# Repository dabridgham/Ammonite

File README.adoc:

= Ammonite

Ammonite is an FPGA development board designed to be useful for
building FPGA-based computers.  It was originally designed to be a
platform for my FPGA PDP-10 but it ought to be useful for just about
anyone who's building their own computer with an FPGA.

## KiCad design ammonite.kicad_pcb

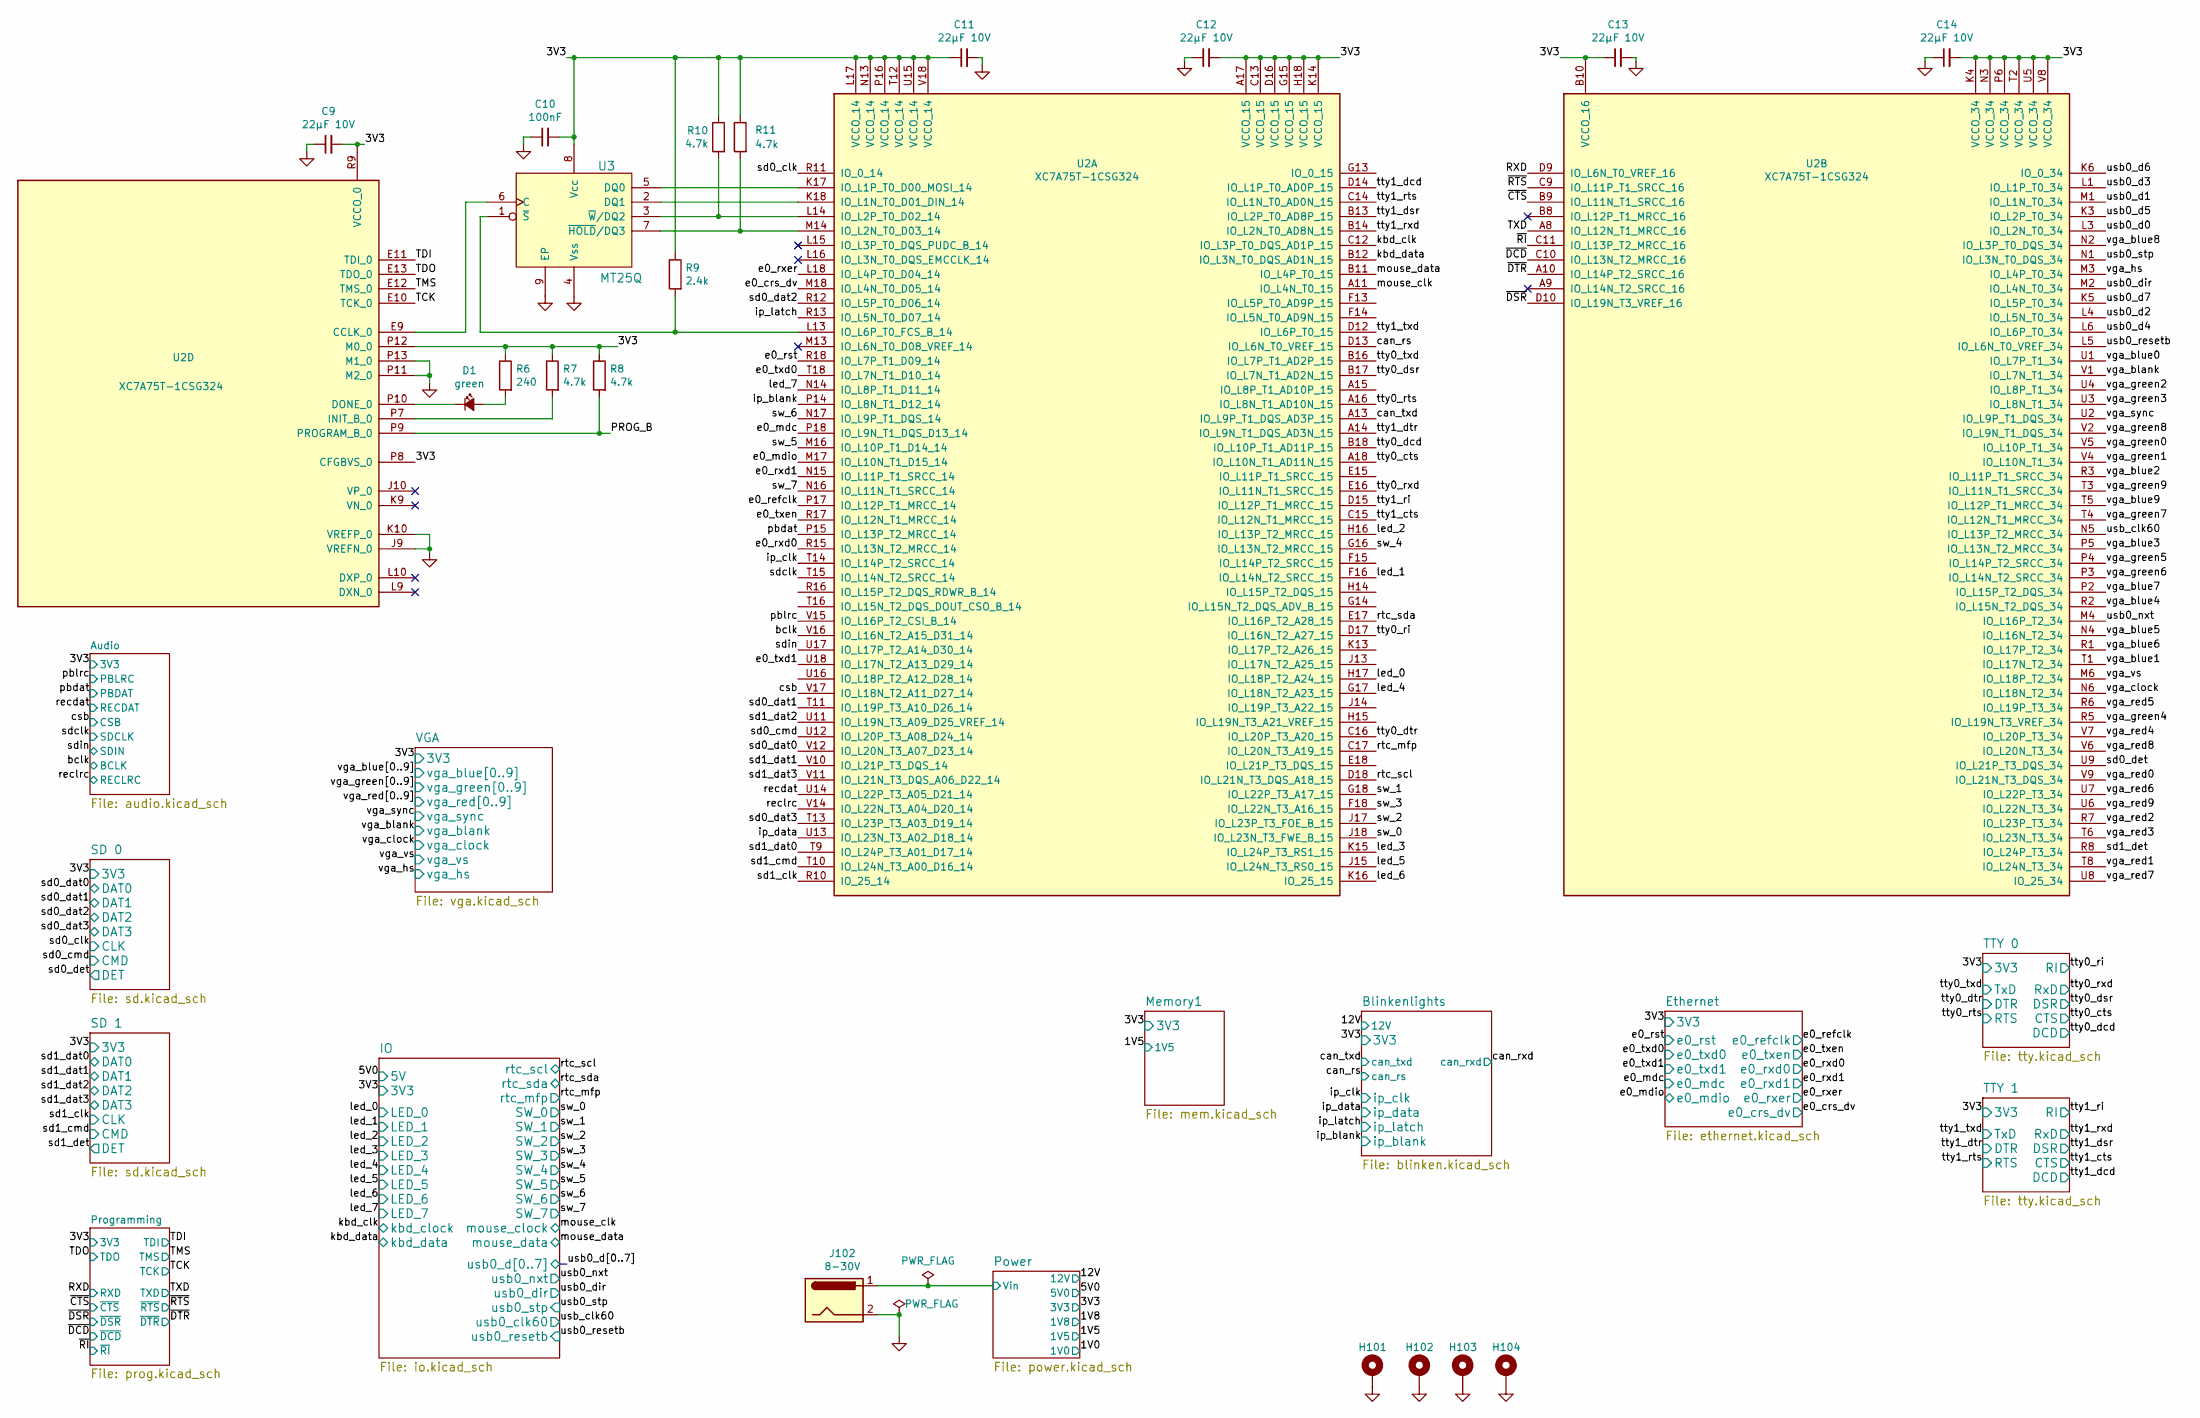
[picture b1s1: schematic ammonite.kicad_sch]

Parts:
C9, C11, C12, C13, C14: 22µF 10V; C_0603_1608Metric
C10: 100nF; C_0603_1608Metric
D1: green; LED_0603_1608Metric
H101, H102, H103, H104: MountingHole_Pad; MountingHole_3.2mm_M3_DIN965_Pad
J102: 8-30V; BarrelJack_CUI_PJ-063AH_Horizontal
R6: 240; R_0603_1608Metric
R7, R8, R10, R11: 4.7k; R_0603_1608Metric
R9: 2.4k; R_0603_1608Metric
U2: XC7A75T-1CSG324; Xilinx_CSG324
U3: MT25Q; DFN-8-1EP_6x5mm_P1.27mm_EP4x4mm

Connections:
/3V3: C9.2, C10.2, C11.1, C12.2, C13.1, C14.2, R6.1, R7.1, R8.1, R9.1, R10.1, R11.1, U2.A17 (VCCO_15), U2.B10 (VCCO_16), U2.C13 (VCCO_15), U2.D16 (VCCO_15), U2.G15 (VCCO_15), U2.H18 (VCCO_15), U2.K4 (VCCO_34), U2.K14 (VCCO_15), U2.L17 (VCCO_14), U2.N3 (VCCO_34), U2.N13 (VCCO_14), U2.P6 (VCCO_34), U2.P8 (CFGBVS_0), U2.P12 (M0_0), U2.P16 (VCCO_14), U2.R9 (VCCO_0), U2.T2 (VCCO_34), U2.T12 (VCCO_14), U2.U5 (VCCO_34), U2.U15 (VCCO_14), U2.V8 (VCCO_34), U2.V18 (VCCO_14), U3.8 (Vcc); also elsewhere on the board
/PROG_B: R8.2, U2.P9 (PROGRAM_B_0)
/Power/Vin: J102.1; also elsewhere on the board
/RXD: U2.D9 (IO_L6N_T0_VREF_16); also elsewhere on the board
/TCK: U2.E10 (TCK_0); also elsewhere on the board
/TDI: U2.E11 (TDI_0); also elsewhere on the board
/TDO: U2.E13 (TDO_0); also elsewhere on the board
/TMS: U2.E12 (TMS_0); also elsewhere on the board
/TXD: U2.A8 (IO_L12N_T1_MRCC_16); also elsewhere on the board
/bclk: U2.V16 (IO_L16N_T2_A15_D31_14); also elsewhere on the board
/can_rs: U2.D13 (IO_L6N_T0_VREF_15); also elsewhere on the board
/can_txd: U2.A13 (IO_L9P_T1_DQS_AD3P_15); also elsewhere on the board
/csb: U2.V17 (IO_L18N_T2_A11_D27_14); also elsewhere on the board
/e0_crs_dv: U2.M18 (IO_L4N_T0_D05_14); also elsewhere on the board
/e0_mdc: U2.P18 (IO_L9N_T1_DQS_D13_14); also elsewhere on the board
/e0_mdio: U2.M17 (IO_L10N_T1_D15_14); also elsewhere on the board
/e0_refclk: U2.P17 (IO_L12P_T1_MRCC_14); also elsewhere on the board
/e0_rst: U2.R18 (IO_L7P_T1_D09_14); also elsewhere on the board
/e0_rxd0: U2.R15 (IO_L13N_T2_MRCC_14); also elsewhere on the board
/e0_rxd1: U2.N15 (IO_L11P_T1_SRCC_14); also elsewhere on the board
/e0_rxer: U2.L18 (IO_L4P_T0_D04_14); also elsewhere on the board
/e0_txd0: U2.T18 (IO_L7N_T1_D10_14); also elsewhere on the board
/e0_txd1: U2.U18 (IO_L17N_T2_A13_D29_14); also elsewhere on the board
/e0_txen: U2.R17 (IO_L12N_T1_MRCC_14); also elsewhere on the board
/ip_blank: U2.P14 (IO_L8N_T1_D12_14); also elsewhere on the board
/ip_clk: U2.T14 (IO_L14P_T2_SRCC_14); also elsewhere on the board
/ip_data: U2.U13 (IO_L23N_T3_A02_D18_14); also elsewhere on the board
/ip_latch: U2.R13 (IO_L5N_T0_D07_14); also elsewhere on the board
/kbd_clk: U2.C12 (IO_L3P_T0_DQS_AD1P_15); also elsewhere on the board
/kbd_data: U2.B12 (IO_L3N_T0_DQS_AD1N_15); also elsewhere on the board
/led_0: U2.H17 (IO_L18P_T2_A24_15); also elsewhere on the board
/led_1: U2.F16 (IO_L14N_T2_SRCC_15); also elsewhere on the board
/led_2: U2.H16 (IO_L13P_T2_MRCC_15); also elsewhere on the board
/led_3: U2.K15 (IO_L24P_T3_RS1_15); also elsewhere on the board
/led_4: U2.G17 (IO_L18N_T2_A23_15); also elsewhere on the board
/led_5: U2.J15 (IO_L24N_T3_RS0_15); also elsewhere on the board
/led_6: U2.K16 (IO_25_15); also elsewhere on the board
/led_7: U2.N14 (IO_L8P_T1_D11_14); also elsewhere on the board
/mouse_clk: U2.A11 (IO_L4N_T0_15); also elsewhere on the board
/mouse_data: U2.B11 (IO_L4P_T0_15); also elsewhere on the board
/pbdat: U2.P15 (IO_L13P_T2_MRCC_14); also elsewhere on the board
/pblrc: U2.V15 (IO_L16P_T2_CSI_B_14); also elsewhere on the board
/recdat: U2.U14 (IO_L22P_T3_A05_D21_14); also elsewhere on the board
/reclrc: U2.V14 (IO_L22N_T3_A04_D20_14); also elsewhere on the board
/rtc_mfp: U2.C17 (IO_L20N_T3_A19_15); also elsewhere on the board
/rtc_scl: U2.D18 (IO_L21N_T3_DQS_A18_15); also elsewhere on the board
/rtc_sda: U2.E17 (IO_L16P_T2_A28_15); also elsewhere on the board
/sd0_clk: U2.R11 (IO_0_14); also elsewhere on the board
/sd0_cmd: U2.U12 (IO_L20P_T3_A08_D24_14); also elsewhere on the board
/sd0_dat0: U2.V12 (IO_L20N_T3_A07_D23_14); also elsewhere on the board
/sd0_dat1: U2.T11 (IO_L19P_T3_A10_D26_14); also elsewhere on the board
/sd0_dat2: U2.R12 (IO_L5P_T0_D06_14); also elsewhere on the board
/sd0_dat3: U2.T13 (IO_L23P_T3_A03_D19_14); also elsewhere on the board
/sd0_det: U2.U9 (IO_L21P_T3_DQS_34); also elsewhere on the board
/sd1_clk: U2.R10 (IO_25_14); also elsewhere on the board
/sd1_cmd: U2.T10 (IO_L24N_T3_A00_D16_14); also elsewhere on the board
/sd1_dat0: U2.T9 (IO_L24P_T3_A01_D17_14); also elsewhere on the board
/sd1_dat1: U2.V10 (IO_L21P_T3_DQS_14); also elsewhere on the board
/sd1_dat2: U2.U11 (IO_L19N_T3_A09_D25_VREF_14); also elsewhere on the board
/sd1_dat3: U2.V11 (IO_L21N_T3_DQS_A06_D22_14); also elsewhere on the board
/sd1_det: U2.R8 (IO_L24P_T3_34); also elsewhere on the board
/sdclk: U2.T15 (IO_L14N_T2_SRCC_14); also elsewhere on the board
/sdin: U2.U17 (IO_L17P_T2_A14_D30_14); also elsewhere on the board
/sw_0: U2.J18 (IO_L23N_T3_FWE_B_15); also elsewhere on the board
/sw_1: U2.G18 (IO_L22P_T3_A17_15); also elsewhere on the board
/sw_2: U2.J17 (IO_L23P_T3_FOE_B_15); also elsewhere on the board
/sw_3: U2.F18 (IO_L22N_T3_A16_15); also elsewhere on the board
/sw_4: U2.G16 (IO_L13N_T2_MRCC_15); also elsewhere on the board
/sw_5: U2.M16 (IO_L10P_T1_D14_14); also elsewhere on the board
/sw_6: U2.N17 (IO_L9P_T1_DQS_14); also elsewhere on the board
/sw_7: U2.N16 (IO_L11N_T1_SRCC_14); also elsewhere on the board
/tty0_cts: U2.A18 (IO_L10N_T1_AD11N_15); also elsewhere on the board
/tty0_dcd: U2.B18 (IO_L10P_T1_AD11P_15); also elsewhere on the board
/tty0_dsr: U2.B17 (IO_L7N_T1_AD2N_15); also elsewhere on the board
/tty0_dtr: U2.C16 (IO_L20P_T3_A20_15); also elsewhere on the board
/tty0_ri: U2.D17 (IO_L16N_T2_A27_15); also elsewhere on the board
/tty0_rts: U2.A16 (IO_L8N_T1_AD10N_15); also elsewhere on the board
/tty0_rxd: U2.E16 (IO_L11N_T1_SRCC_15); also elsewhere on the board
/tty0_txd: U2.B16 (IO_L7P_T1_AD2P_15); also elsewhere on the board
/tty1_cts: U2.C15 (IO_L12N_T1_MRCC_15); also elsewhere on the board
/tty1_dcd: U2.D14 (IO_L1P_T0_AD0P_15); also elsewhere on the board
/tty1_dsr: U2.B13 (IO_L2P_T0_AD8P_15); also elsewhere on the board
/tty1_dtr: U2.A14 (IO_L9N_T1_DQS_AD3N_15); also elsewhere on the board
/tty1_ri: U2.D15 (IO_L12P_T1_MRCC_15); also elsewhere on the board
/tty1_rts: U2.C14 (IO_L1N_T0_AD0N_15); also elsewhere on the board
/tty1_rxd: U2.B14 (IO_L2N_T0_AD8N_15); also elsewhere on the board
/tty1_txd: U2.D12 (IO_L6P_T0_15); also elsewhere on the board
/usb0_d0: U2.L3 (IO_L2N_T0_34); also elsewhere on the board
/usb0_d1: U2.M1 (IO_L1N_T0_34); also elsewhere on the board
/usb0_d2: U2.L4 (IO_L5N_T0_34); also elsewhere on the board
/usb0_d3: U2.L1 (IO_L1P_T0_34); also elsewhere on the board
/usb0_d4: U2.L6 (IO_L6P_T0_34); also elsewhere on the board
/usb0_d5: U2.K3 (IO_L2P_T0_34); also elsewhere on the board
/usb0_d6: U2.K6 (IO_0_34); also elsewhere on the board
/usb0_d7: U2.K5 (IO_L5P_T0_34); also elsewhere on the board
/usb0_dir: U2.M2 (IO_L4N_T0_34); also elsewhere on the board
/usb0_nxt: U2.M4 (IO_L16P_T2_34); also elsewhere on the board
/usb0_resetb: U2.L5 (IO_L6N_T0_VREF_34); also elsewhere on the board
/usb0_stp: U2.N1 (IO_L3N_T0_DQS_34); also elsewhere on the board
/usb_clk60: U2.N5 (IO_L13P_T2_MRCC_34); also elsewhere on the board
/vga_blank: U2.V1 (IO_L7N_T1_34); also elsewhere on the board
/vga_blue0: U2.U1 (IO_L7P_T1_34); also elsewhere on the board
/vga_blue1: U2.T1 (IO_L17N_T2_34); also elsewhere on the board
/vga_blue2: U2.R3 (IO_L11P_T1_SRCC_34); also elsewhere on the board
/vga_blue3: U2.P5 (IO_L13N_T2_MRCC_34); also elsewhere on the board
/vga_blue4: U2.R2 (IO_L15N_T2_DQS_34); also elsewhere on the board
/vga_blue5: U2.N4 (IO_L16N_T2_34); also elsewhere on the board
/vga_blue6: U2.R1 (IO_L17P_T2_34); also elsewhere on the board
/vga_blue7: U2.P2 (IO_L15P_T2_DQS_34); also elsewhere on the board
/vga_blue8: U2.N2 (IO_L3P_T0_DQS_34); also elsewhere on the board
/vga_blue9: U2.T5 (IO_L12P_T1_MRCC_34); also elsewhere on the board
/vga_clock: U2.N6 (IO_L18N_T2_34); also elsewhere on the board
/vga_green0: U2.V5 (IO_L10P_T1_34); also elsewhere on the board
/vga_green1: U2.V4 (IO_L10N_T1_34); also elsewhere on the board
/vga_green2: U2.U4 (IO_L8P_T1_34); also elsewhere on the board
/vga_green3: U2.U3 (IO_L8N_T1_34); also elsewhere on the board
/vga_green4: U2.R5 (IO_L19N_T3_VREF_34); also elsewhere on the board
/vga_green5: U2.P4 (IO_L14P_T2_SRCC_34); also elsewhere on the board
/vga_green6: U2.P3 (IO_L14N_T2_SRCC_34); also elsewhere on the board
/vga_green7: U2.T4 (IO_L12N_T1_MRCC_34); also elsewhere on the board
/vga_green8: U2.V2 (IO_L9N_T1_DQS_34); also elsewhere on the board
/vga_green9: U2.T3 (IO_L11N_T1_SRCC_34); also elsewhere on the board
/vga_hs: U2.M3 (IO_L4P_T0_34); also elsewhere on the board
/vga_red0: U2.V9 (IO_L21N_T3_DQS_34); also elsewhere on the board
/vga_red1: U2.T8 (IO_L24N_T3_34); also elsewhere on the board
/vga_red2: U2.R7 (IO_L23P_T3_34); also elsewhere on the board
/vga_red3: U2.T6 (IO_L23N_T3_34); also elsewhere on the board
/vga_red4: U2.V7 (IO_L20P_T3_34); also elsewhere on the board
/vga_red5: U2.R6 (IO_L19P_T3_34); also elsewhere on the board
/vga_red6: U2.U7 (IO_L22P_T3_34); also elsewhere on the board
/vga_red7: U2.U8 (IO_25_34); also elsewhere on the board
/vga_red8: U2.V6 (IO_L20N_T3_34); also elsewhere on the board
/vga_red9: U2.U6 (IO_L22N_T3_34); also elsewhere on the board
/vga_sync: U2.U2 (IO_L9P_T1_DQS_34); also elsewhere on the board
/vga_vs: U2.M6 (IO_L18P_T2_34); also elsewhere on the board
/~CTS: U2.B9 (IO_L11N_T1_SRCC_16); also elsewhere on the board
/~DCD: U2.C10 (IO_L13N_T2_MRCC_16); also elsewhere on the board
/~DSR: U2.D10 (IO_L19N_T3_VREF_16); also elsewhere on the board
/~DTR: U2.A10 (IO_L14P_T2_SRCC_16); also elsewhere on the board
/~RI: U2.C11 (IO_L13P_T2_MRCC_16); also elsewhere on the board
/~RTS: U2.C9 (IO_L11P_T1_SRCC_16); also elsewhere on the board
GND: C9.1, C10.1, C11.2, C12.1, C13.2, C14.1, H101.1, H102.1, H103.1, H104.1, J102.2, U2.J9 (VREFN_0), U2.K10 (VREFP_0), U2.P11 (M2_0), U2.P13 (M1_0), U3.4 (Vss), U3.9 (EP); also elsewhere on the board
unnamed: D1.1 (K), U2.P10 (DONE_0)
unnamed: D1.2 (A), R6.2
unnamed: R7.2, U2.P7 (INIT_B_0)
unnamed: R9.2, U2.L13 (IO_L6P_T0_FCS_B_14), U3.1 (~S)
unnamed: R10.2, U2.L14 (IO_L2P_T0_D02_14), U3.3 (~W/DQ2)
unnamed: R11.2, U2.M14 (IO_L2N_T0_D03_14), U3.7 (~HOLD/DQ3)
unnamed: U2.E9 (CCLK_0), U3.6 (C)
unnamed: U2.K17 (IO_L1P_T0_D00_MOSI_14), U3.5 (DQ0)
unnamed: U2.K18 (IO_L1N_T0_D01_DIN_14), U3.2 (DQ1)

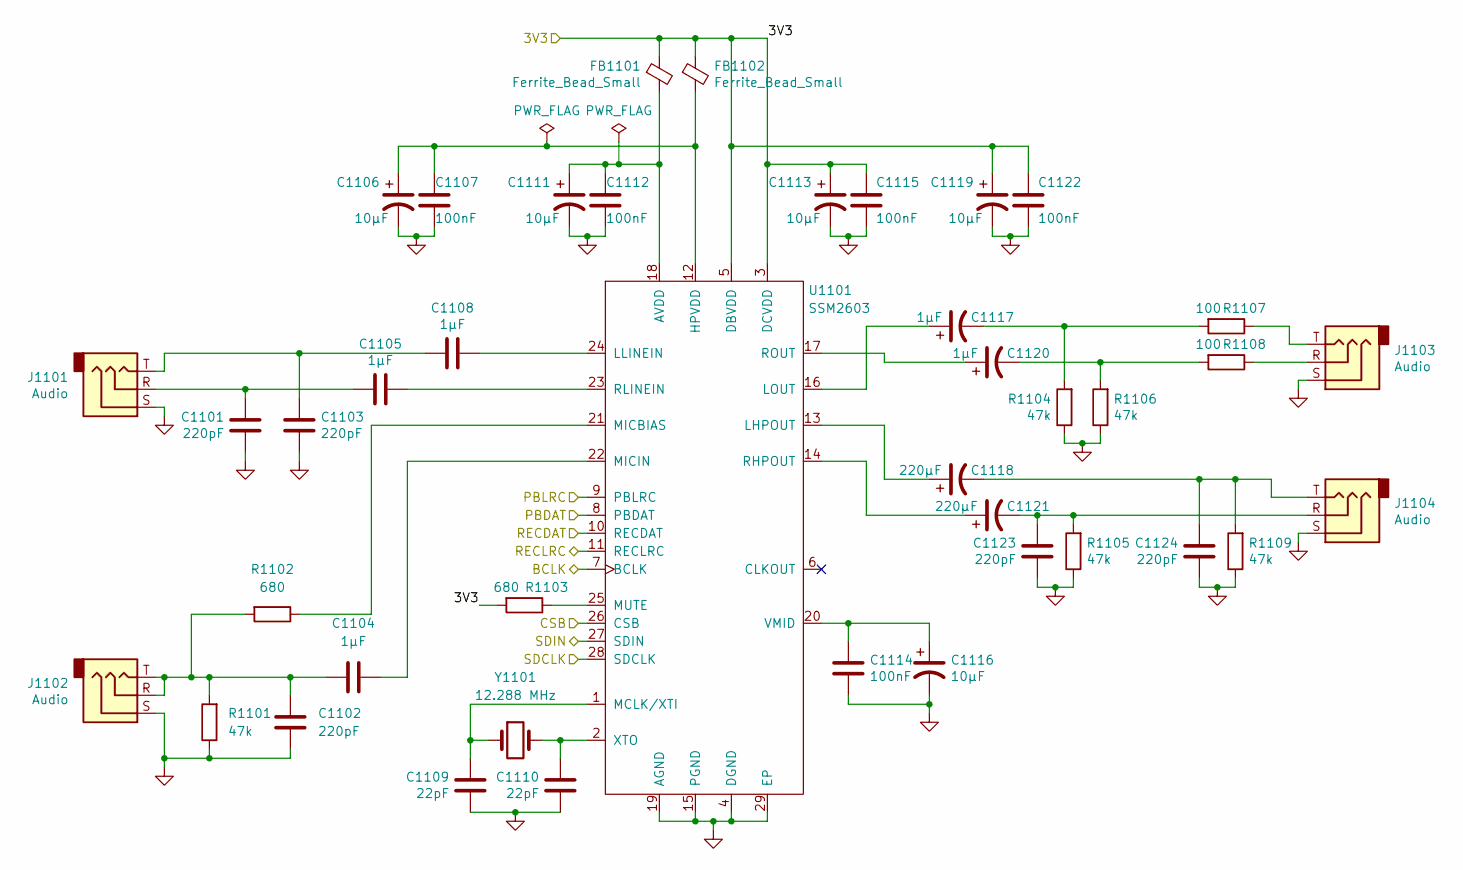
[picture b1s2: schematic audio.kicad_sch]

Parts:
C1101, C1102, C1103, C1123, C1124: 220pF; C_0603_1608Metric
C1104, C1105, C1108, C1117, C1120: 1µF; C_0603_1608Metric
C1106, C1111, C1113, C1116, C1119: 10µF; C_0603_1608Metric
C1107, C1112, C1114, C1115, C1122: 100nF; C_0603_1608Metric
C1109, C1110: 22pF; C_0603_1608Metric
C1118, C1121: 220µF; C_0603_1608Metric
FB1101, FB1102: Ferrite_Bead_Small; L_0603_1608Metric
J1101, J1102, J1103, J1104: Audio; CUI_SJ-3523-SMT-TR
R1101, R1104, R1105, R1106, R1109: 47k; R_0603_1608Metric
R1102, R1103: 680; R_0603_1608Metric
R1107, R1108: 100; R_0603_1608Metric
U1101: SSM2603; SSM2603CPZ-REEL7
Y1101: 12.288 MHz; Crystal_SMD_Abracon_ABM3-2Pin_5.0x3.2mm

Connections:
/3V3: C1113.1, C1115.1, C1119.1, C1122.1, FB1101.1, FB1102.1, R1103.2, U1101.3 (DCVDD), U1101.5 (DBVDD); also elsewhere on the board
/bclk: U1101.7 (BCLK); also elsewhere on the board
/csb: U1101.26 (CSB); also elsewhere on the board
/pbdat: U1101.8 (PBDAT); also elsewhere on the board
/pblrc: U1101.9 (PBLRC); also elsewhere on the board
/recdat: U1101.10 (RECDAT); also elsewhere on the board
/reclrc: U1101.11 (RECLRC); also elsewhere on the board
/sdclk: U1101.28 (SDCLK); also elsewhere on the board
/sdin: U1101.27 (SDIN); also elsewhere on the board
GND: C1101.2, C1102.2, C1103.2, C1106.2, C1107.2, C1109.2, C1110.2, C1111.2, C1112.2, C1113.2, C1114.2, C1115.2, C1116.2, C1119.2, C1122.2, C1123.2, C1124.2, J1101.S, J1102.S, J1103.S, J1104.S, R1101.1, R1104.1, R1105.1, R1106.1, R1109.1, U1101.4 (DGND), U1101.15 (PGND), U1101.19 (AGND), U1101.29 (EP); also elsewhere on the board
unnamed: C1101.1, C1105.1, J1101.R
unnamed: C1102.1, C1104.1, J1102.R, J1102.T, R1101.2, R1102.2
unnamed: C1103.1, C1108.1, J1101.T
unnamed: C1104.2, U1101.22 (MICIN)
unnamed: C1105.2, U1101.23 (RLINEIN)
unnamed: C1106.1, C1107.1, FB1102.2, U1101.12 (HPVDD)
unnamed: C1108.2, U1101.24 (LLINEIN)
unnamed: C1109.1, U1101.1 (MCLK/XTI), Y1101.1
unnamed: C1110.1, U1101.2 (XTO), Y1101.2
unnamed: C1111.1, C1112.1, FB1101.2, U1101.18 (AVDD)
unnamed: C1114.1, C1116.1, U1101.20 (VMID)
unnamed: C1117.1, U1101.16 (LOUT)
unnamed: C1117.2, R1104.2, R1107.2
unnamed: C1118.1, U1101.13 (LHPOUT)
unnamed: C1118.2, C1124.1, J1104.T, R1109.2
unnamed: C1120.1, U1101.17 (ROUT)
unnamed: C1120.2, R1106.2, R1108.2
unnamed: C1121.1, U1101.14 (RHPOUT)
unnamed: C1121.2, C1123.1, J1104.R, R1105.2
unnamed: J1103.R, R1108.1
unnamed: J1103.T, R1107.1
unnamed: R1102.1, U1101.21 (MICBIAS)
unnamed: R1103.1, U1101.25 (MUTE)

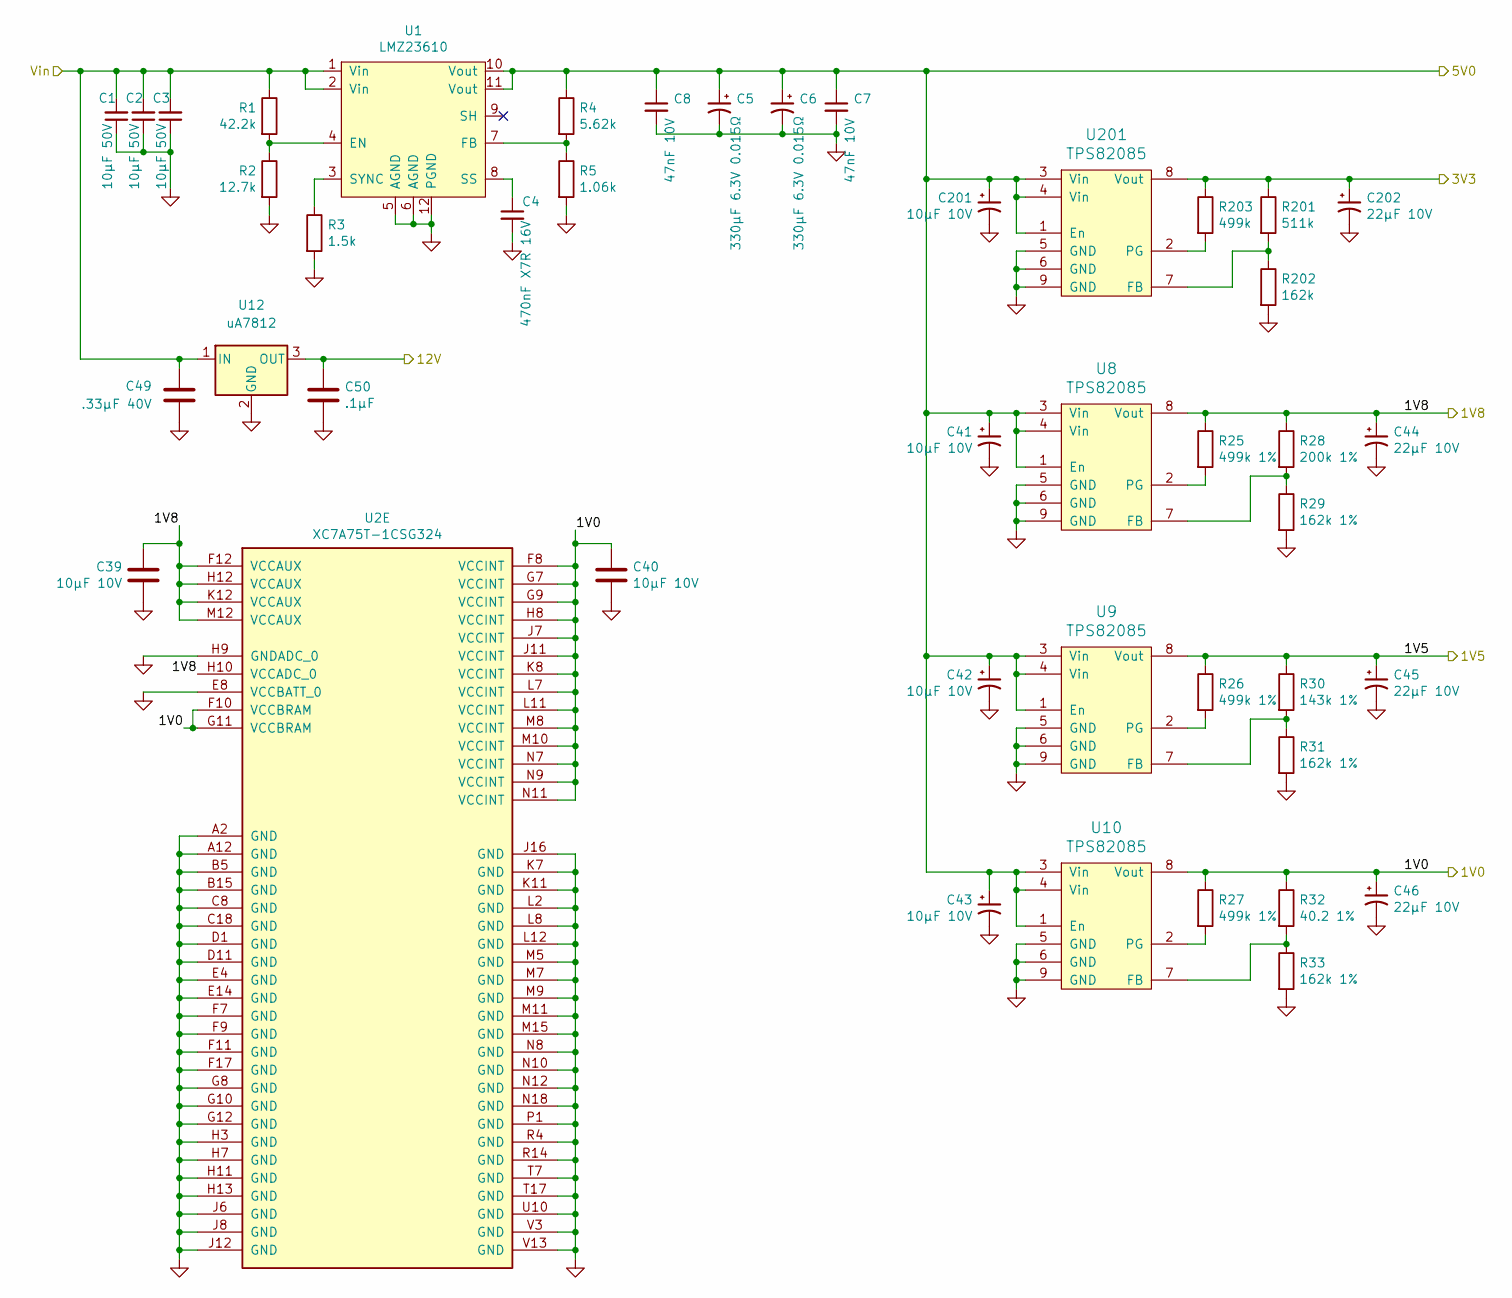
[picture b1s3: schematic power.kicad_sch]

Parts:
C1, C2, C3: 10µF 50V; C_1210_3225Metric
C4: 470nF X7R 16V; C_0805_2012Metric
C5, C6: 330µF 6.3V 0.015Ω; CP_EIA-7343-31_Kemet-D
C7, C8: 47nF 10V; C_1206_3216Metric
C39, C40, C41, C42, C43, C201: 10µF 10V; C_0603_1608Metric
C44, C45, C46, C202: 22µF 10V; C_0603_1608Metric
C49: .33µF 40V; C_0603_1608Metric
C50: .1µF; C_0603_1608Metric
R1: 42.2k; R_0805_2012Metric
R2: 12.7k; R_0805_2012Metric
R3: 1.5k; R_0805_2012Metric
R4: 5.62k; R_0805_2012Metric
R5: 1.06k; R_0805_2012Metric
R25, R26, R27: 499k 1%; R_0603_1608Metric
R28: 200k 1%; R_0603_1608Metric
R29, R31, R33: 162k 1%; R_0603_1608Metric
R30: 143k 1%; R_0603_1608Metric
R32: 40.2 1%; R_0603_1608Metric
R201: 511k; R_0603_1608Metric
R202: 162k; R_0603_1608Metric
R203: 499k; R_0603_1608Metric
U1: LMZ23610; Texas_NDY0011A
U2: XC7A75T-1CSG324; Xilinx_CSG324
U8, U9, U10, U201: TPS82085; Texas_SIL0008D_MicroSiP-8-1EP_2.8x3mm_P0.65mm_EP1.1x1.9mm_T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
U12: uA7812; TO-263-3_TabPin2

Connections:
/1V0: C40.1, C46.1, R27.1, R32.1, U2.F8 (VCCINT), U2.F10 (VCCBRAM), U2.G7 (VCCINT), U2.G9 (VCCINT), U2.G11 (VCCBRAM), U2.H8 (VCCINT), U2.J7 (VCCINT), U2.J11 (VCCINT), U2.K8 (VCCINT), U2.L7 (VCCINT), U2.L11 (VCCINT), U2.M8 (VCCINT), U2.M10 (VCCINT), U2.N7 (VCCINT), U2.N9 (VCCINT), U2.N11 (VCCINT), U10.8 (Vout)
/1V5: C45.1, R26.1, R30.1, U9.8 (Vout); also elsewhere on the board
/1V8: C39.1, C44.1, R25.1, R28.1, U2.F12 (VCCAUX), U2.H10 (VCCADC_0), U2.H12 (VCCAUX), U2.K12 (VCCAUX), U2.M12 (VCCAUX), U8.8 (Vout)
/3V3: C202.1, R201.1, R203.1, U201.8 (Vout); also elsewhere on the board
/5V0: C5.1, C6.1, C7.1, C8.1, C41.1, C42.1, C43.1, C201.1, R4.1, U1.10 (Vout), U1.11 (Vout), U8.1 (En), U8.3 (Vin), U8.4 (Vin), U9.1 (En), U9.3 (Vin), U9.4 (Vin), U10.1 (En), U10.3 (Vin), U10.4 (Vin), U201.1 (En), U201.3 (Vin), U201.4 (Vin); also elsewhere on the board
/12V: C50.1, U12.3 (OUT); also elsewhere on the board
/Power/Vin: C1.2, C2.2, C3.2, C49.1, R1.1, U1.1 (Vin), U1.2 (Vin), U12.1 (IN); also elsewhere on the board
GND: C1.1, C2.1, C3.1, C4.2, C5.2, C6.2, C7.2, C8.2, C39.2, C40.2, C41.2, C42.2, C43.2, C44.2, C45.2, C46.2, C49.2, C50.2, C201.2, C202.2, R2.2, R3.2, R5.2, R29.2, R31.2, R33.2, R202.2, U1.5 (AGND), U1.6 (AGND), U1.12 (PGND), U2.A2 (GND), U2.A12 (GND), U2.B5 (GND), U2.B15 (GND), U2.C8 (GND), U2.C18 (GND), U2.D1 (GND), U2.D11 (GND), U2.E4 (GND), U2.E8 (VCCBATT_0), U2.E14 (GND), U2.F7 (GND), U2.F9 (GND), U2.F11 (GND), U2.F17 (GND), U2.G8 (GND), U2.G10 (GND), U2.G12 (GND), U2.H3 (GND), U2.H7 (GND), U2.H9 (GNDADC_0), U2.H11 (GND), U2.H13 (GND), U2.J6 (GND), U2.J8 (GND), U2.J12 (GND), U2.J16 (GND), U2.K7 (GND), U2.K11 (GND), U2.L2 (GND), U2.L8 (GND), U2.L12 (GND), U2.M5 (GND), U2.M7 (GND), U2.M9 (GND), U2.M11 (GND), U2.M15 (GND), U2.N8 (GND), U2.N10 (GND), U2.N12 (GND), U2.N18 (GND), U2.P1 (GND), U2.R4 (GND), U2.R14 (GND), U2.T7 (GND), U2.T17 (GND), U2.U10 (GND), U2.V3 (GND), U2.V13 (GND), U8.5 (GND), U8.6 (GND), U8.9 (GND), U9.5 (GND), U9.6 (GND), U9.9 (GND), U10.5 (GND), U10.6 (GND), U10.9 (GND), U12.2 (GND), U201.5 (GND), U201.6 (GND), U201.9 (GND); also elsewhere on the board
unnamed: C4.1, U1.8 (SS)
unnamed: R1.2, R2.1, U1.4 (EN)
unnamed: R3.1, U1.3 (SYNC)
unnamed: R4.2, R5.1, U1.7 (FB)
unnamed: R25.2, U8.2 (PG)
unnamed: R26.2, U9.2 (PG)
unnamed: R27.2, U10.2 (PG)
unnamed: R28.2, R29.1, U8.7 (FB)
unnamed: R30.2, R31.1, U9.7 (FB)
unnamed: R32.2, R33.1, U10.7 (FB)
unnamed: R201.2, R202.1, U201.7 (FB)
unnamed: R203.2, U201.2 (PG)

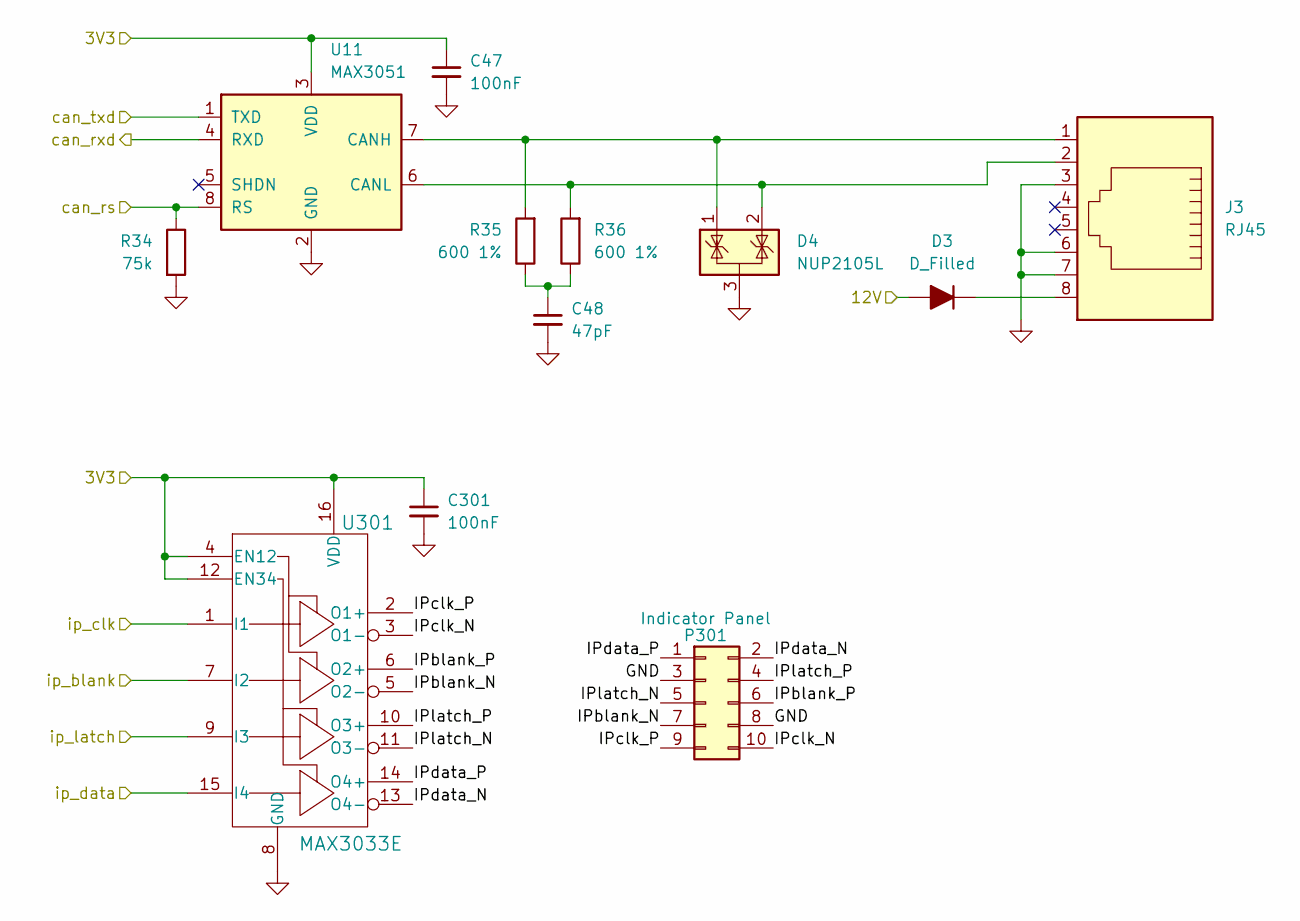
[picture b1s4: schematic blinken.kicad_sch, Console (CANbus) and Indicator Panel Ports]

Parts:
C47, C301: 100nF; C_0603_1608Metric
C48: 47pF; C_0603_1608Metric
D3: D_Filled; D_0603_1608Metric
D4: NUP2105L; SOT-23
J3: RJ45; RJ45_Amphenol_54602-x08_Horizontal
P301: Indicator Panel; PinHeader_2x05_P2.54mm_Vertical_shrouded
R34: 75k; R_0603_1608Metric
R35, R36: 600 1%; R_0603_1608Metric
U11: MAX3051; SOT-23-8
U301: MAX3033E; TSSOP-16_4.4x5mm_P0.65mm

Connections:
/3V3: C47.1, C301.1, U11.3 (VDD), U301.4 (EN12), U301.12 (EN34), U301.16 (VDD); also elsewhere on the board
/12V: D3.2 (A); also elsewhere on the board
/Blinkenlights/IPblank_N: P301.7, U301.5 (O2-)
/Blinkenlights/IPblank_P: P301.6, U301.6 (O2+)
/Blinkenlights/IPclk_N: P301.10, U301.3 (O1-)
/Blinkenlights/IPclk_P: P301.9, U301.2 (O1+)
/Blinkenlights/IPdata_N: P301.2, U301.13 (O4-)
/Blinkenlights/IPdata_P: P301.1, U301.14 (O4+)
/Blinkenlights/IPlatch_N: P301.5, U301.11 (O3-)
/Blinkenlights/IPlatch_P: P301.4, U301.10 (O3+)
/can_rs: R34.1, U11.8 (RS); also elsewhere on the board
/can_rxd: U11.4 (RXD)
/can_txd: U11.1 (TXD); also elsewhere on the board
/ip_blank: U301.7 (I2); also elsewhere on the board
/ip_clk: U301.1 (I1); also elsewhere on the board
/ip_data: U301.15 (I4); also elsewhere on the board
/ip_latch: U301.9 (I3); also elsewhere on the board
GND: C47.2, C48.2, C301.2, D4.3 (A), J3.3, J3.6, J3.7, P301.3, P301.8, R34.2, U11.2 (GND), U301.8 (GND); also elsewhere on the board
unnamed: C48.1, R35.1, R36.1
unnamed: D3.1 (K), J3.8
unnamed: D4.1 (K), J3.1, R35.2, U11.7 (CANH)
unnamed: D4.2 (K), J3.2, R36.2, U11.6 (CANL)

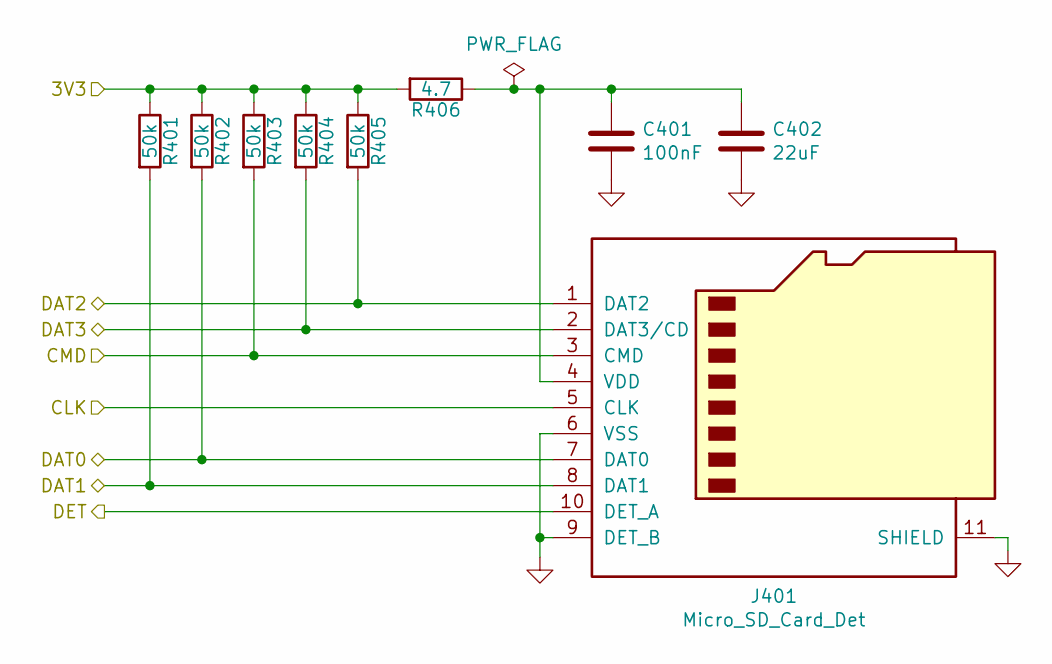
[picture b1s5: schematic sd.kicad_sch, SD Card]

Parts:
C401: 100nF; C_0603_1608Metric
C402: 22uF; C_0603_1608Metric
J401: Micro_SD_Card_Det; AMPHENOL_1140084168
R401, R402, R403, R404, R405: 50k; R_0603_1608Metric
R406: 4.7; R_0603_1608Metric

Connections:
/3V3: R401.1, R402.1, R403.1, R404.1, R405.1, R406.2; also elsewhere on the board
/sd0_clk: J401.5 (CLK); also elsewhere on the board
/sd0_cmd: J401.3 (CMD), R403.2; also elsewhere on the board
/sd0_dat0: J401.7 (DAT0), R402.2; also elsewhere on the board
/sd0_dat1: J401.8 (DAT1), R401.2; also elsewhere on the board
/sd0_dat2: J401.1 (DAT2), R405.2; also elsewhere on the board
/sd0_dat3: J401.2 (DAT3/CD), R404.2; also elsewhere on the board
/sd0_det: J401.10 (DET_A); also elsewhere on the board
GND: C401.2, C402.2, J401.6 (VSS), J401.9 (DET_B), J401.11 (SHIELD); also elsewhere on the board
unnamed: C401.1, C402.1, J401.4 (VDD), R406.1

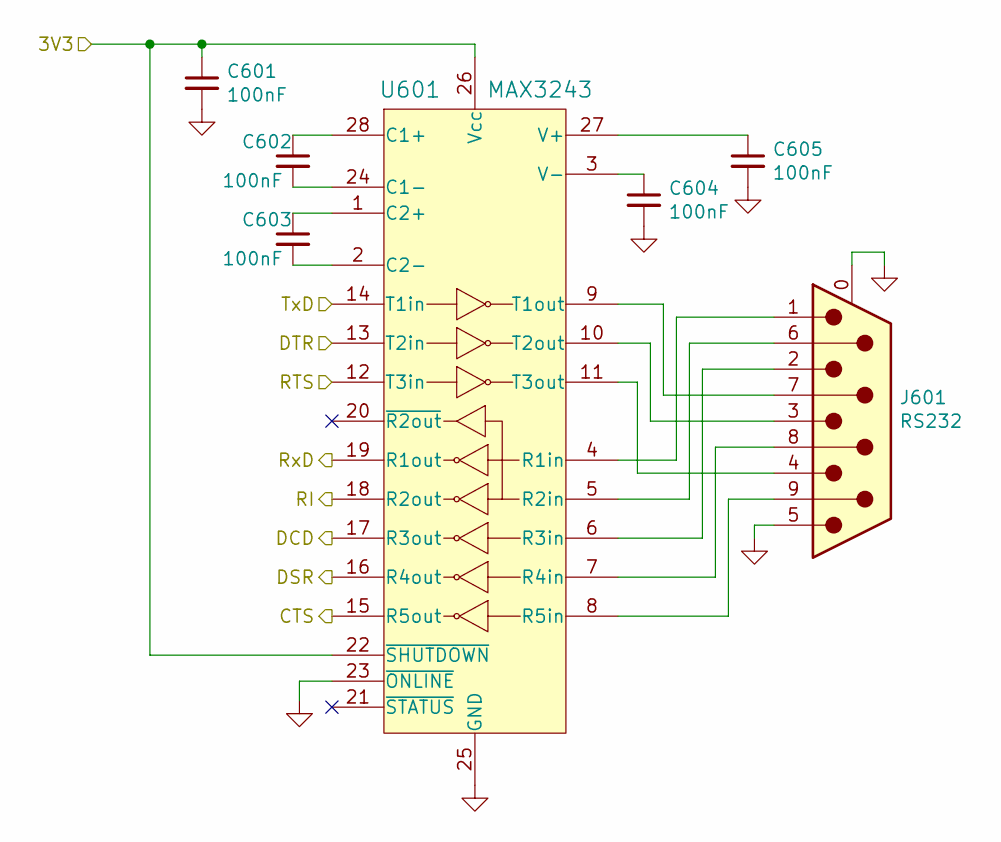
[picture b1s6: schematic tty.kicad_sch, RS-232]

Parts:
C601, C602, C603, C604, C605: 100nF; C_0603_1608Metric
J601: RS232; DSUB-9_Male_Horizontal_P2.77x2.84mm_EdgePinOffset9.90mm_Hou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
U601: MAX3243; TSSOP-28_4.4x9.7mm_P0.65mm

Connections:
/3V3: C601.1, U601.22 (~SHUTDOWN), U601.26 (Vcc); also elsewhere on the board
/tty0_cts: U601.15 (R5out); also elsewhere on the board
/tty0_dcd: U601.17 (R3out); also elsewhere on the board
/tty0_dsr: U601.16 (R4out); also elsewhere on the board
/tty0_dtr: U601.13 (T2in); also elsewhere on the board
/tty0_ri: U601.18 (R2out); also elsewhere on the board
/tty0_rts: U601.12 (T3in); also elsewhere on the board
/tty0_rxd: U601.19 (R1out); also elsewhere on the board
/tty0_txd: U601.14 (T1in); also elsewhere on the board
GND: C601.2, C604.2, C605.2, J601.0 (PAD), J601.5, U601.23 (~ONLINE), U601.25 (GND); also elsewhere on the board
unnamed: C602.1, U601.28 (C1+)
unnamed: C602.2, U601.24 (C1-)
unnamed: C603.1, U601.1 (C2+)
unnamed: C603.2, U601.2 (C2-)
unnamed: C604.1, U601.3 (V-)
unnamed: C605.1, U601.27 (V+)
unnamed: J601.1, U601.4 (R1in)
unnamed: J601.2, U601.6 (R3in)
unnamed: J601.3, U601.10 (T2out)
unnamed: J601.4, U601.11 (T3out)
unnamed: J601.6, U601.5 (R2in)
unnamed: J601.7, U601.9 (T1out)
unnamed: J601.8, U601.7 (R4in)
unnamed: J601.9, U601.8 (R5in)
